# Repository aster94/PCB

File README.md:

# PCB

This is a repo to store some PCB I've made for various projects

In every folder there is a PCB with readme, images, the eagle/KiCad files and a zip archive with the gerber files. All licensed with CC-BY-SA

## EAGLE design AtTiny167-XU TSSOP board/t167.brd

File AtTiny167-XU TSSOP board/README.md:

# AtTiny167-XU TSSOP board

### License

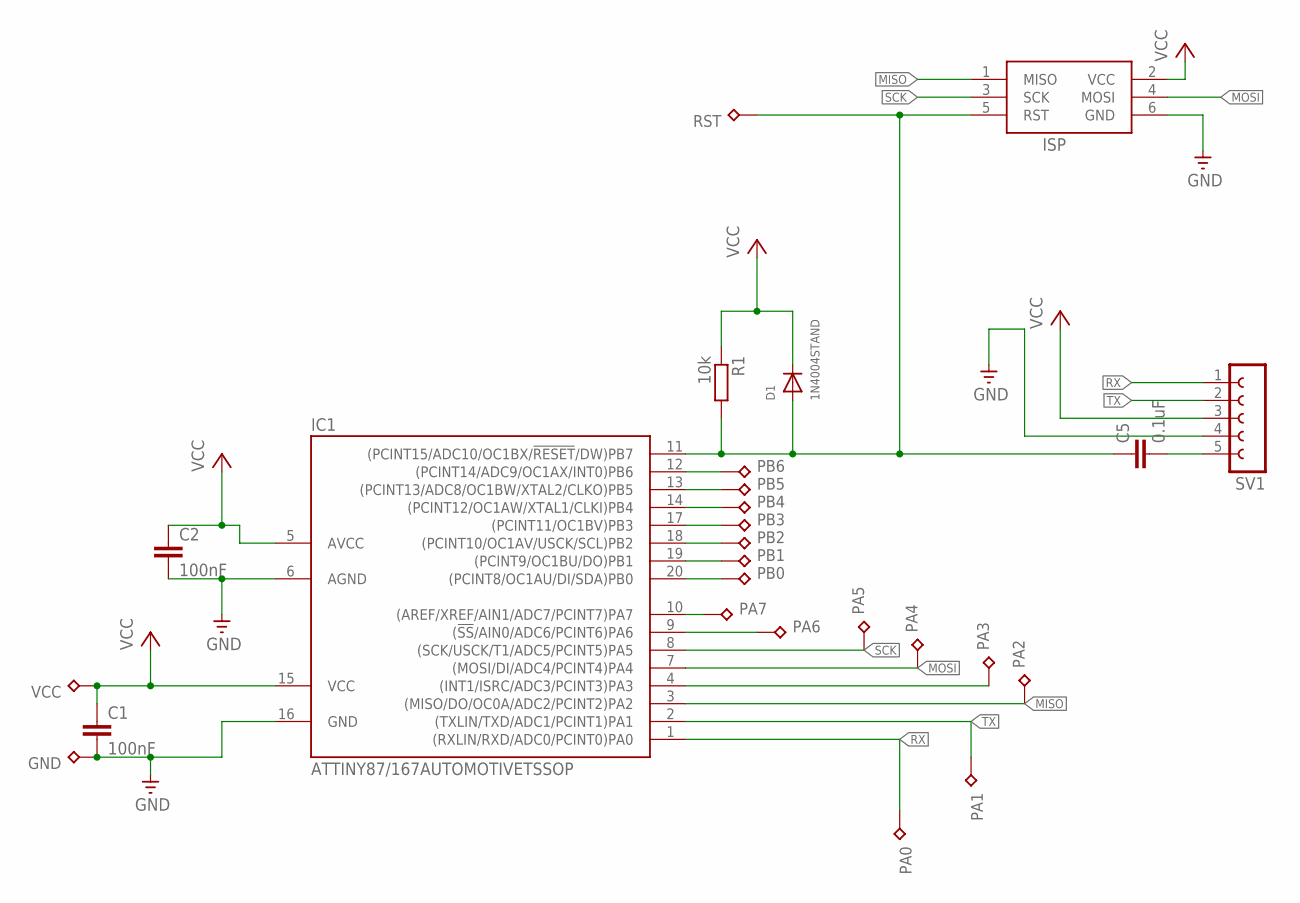
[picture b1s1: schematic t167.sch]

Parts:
C1, C2: 100nF; C0805
C5: 0.1uF; C0805K
D1: 1N4004STAND; SOD-323F
GND: 1XPIN-HEADER
IC1: ATTINY87/167AUTOMOTIVETSSOP; TSSOP20
ISP: AVRISP-6; AVRISP
PA0, PA1, PA2, PA3, PA4, PA5, PA6, PA7: 1XPIN-HEADER
PB0, PB1, PB2, PB3, PB4, PB5, PB6: 1XPIN-HEADER
R1: 10k; M0805
RST: 1XPIN-HEADER
SV1: FE05-1
VCC: 1XPIN-HEADER

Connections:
GND: C1.2, C2.2, GND.P$1, IC1.6 (AGND), IC1.16 (GND), ISP.6 (GND), SV1.4
MISO: IC1.3 ((MISO/DO/OC0A/ADC2/PCINT2)PA2), ISP.1 (MISO), PA2.P$1
MOSI: IC1.7 ((MOSI/DI/ADC4/PCINT4)PA4), ISP.4 (MOSI), PA4.P$1
unnamed: IC1.4 ((INT1/ISRC/ADC3/PCINT3)PA3), PA3.P$1
unnamed: C5.2, SV1.5
unnamed: IC1.9 ((!SS!/AIN0/ADC6/PCINT6)PA6), PA6.P$1
unnamed: IC1.10 ((AREF/XREF/AIN1/ADC7/PCINT7)PA7), PA7.P$1
unnamed: IC1.18 ((PCINT10/OC1AV/USCK/SCL)PB2), PB2.P$1
unnamed: IC1.20 ((PCINT8/OC1AU/DI/SDA)PB0), PB0.P$1
unnamed: IC1.19 ((PCINT9/OC1BU/DO)PB1), PB1.P$1
unnamed: IC1.17 ((PCINT11/OC1BV)PB3), PB3.P$1
unnamed: IC1.14 ((PCINT12/OC1AW/XTAL1/CLKI)PB4), PB4.P$1
unnamed: IC1.13 ((PCINT13/ADC8/OC1BW/XTAL2/CLKO)PB5), PB5.P$1
unnamed: IC1.12 ((PCINT14/ADC9/OC1AX/INT0)PB6), PB6.P$1
RST: C5.1, D1.A, IC1.11 ((PCINT15/ADC10/OC1BX/!RESET!/DW)PB7), ISP.5 (RST), R1.2, RST.P$1
RX: IC1.1 ((RXLIN/RXD/ADC0/PCINT0)PA0), PA0.P$1, SV1.1
SCK: IC1.8 ((SCK/USCK/T1/ADC5/PCINT5)PA5), ISP.3 (SCK), PA5.P$1
TX: IC1.2 ((TXLIN/TXD/ADC1/PCINT1)PA1), PA1.P$1, SV1.2
VCC: C1.1, C2.1, D1.C, IC1.5 (AVCC), IC1.15 (VCC), ISP.2 (VCC), R1.1, SV1.3, VCC.P$1

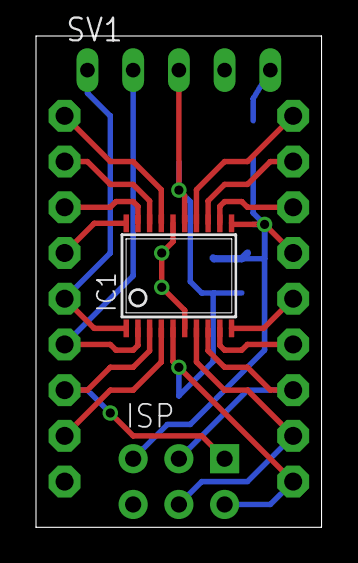
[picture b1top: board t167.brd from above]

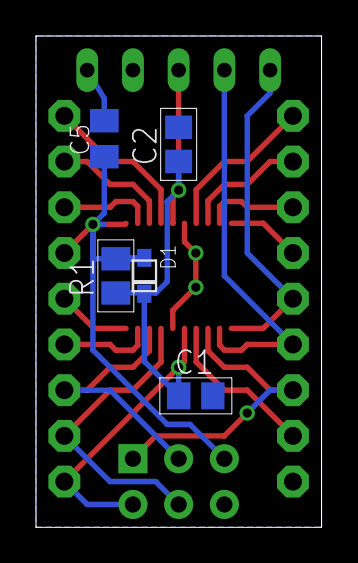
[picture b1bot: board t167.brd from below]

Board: 2 copper layers, 15.9 x 27.3 mm, 26 parts (5 on the bottom side), 19 nets.

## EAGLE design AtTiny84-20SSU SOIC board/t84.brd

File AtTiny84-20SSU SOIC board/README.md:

# AtTiny84-20SSU SOIC board

### License

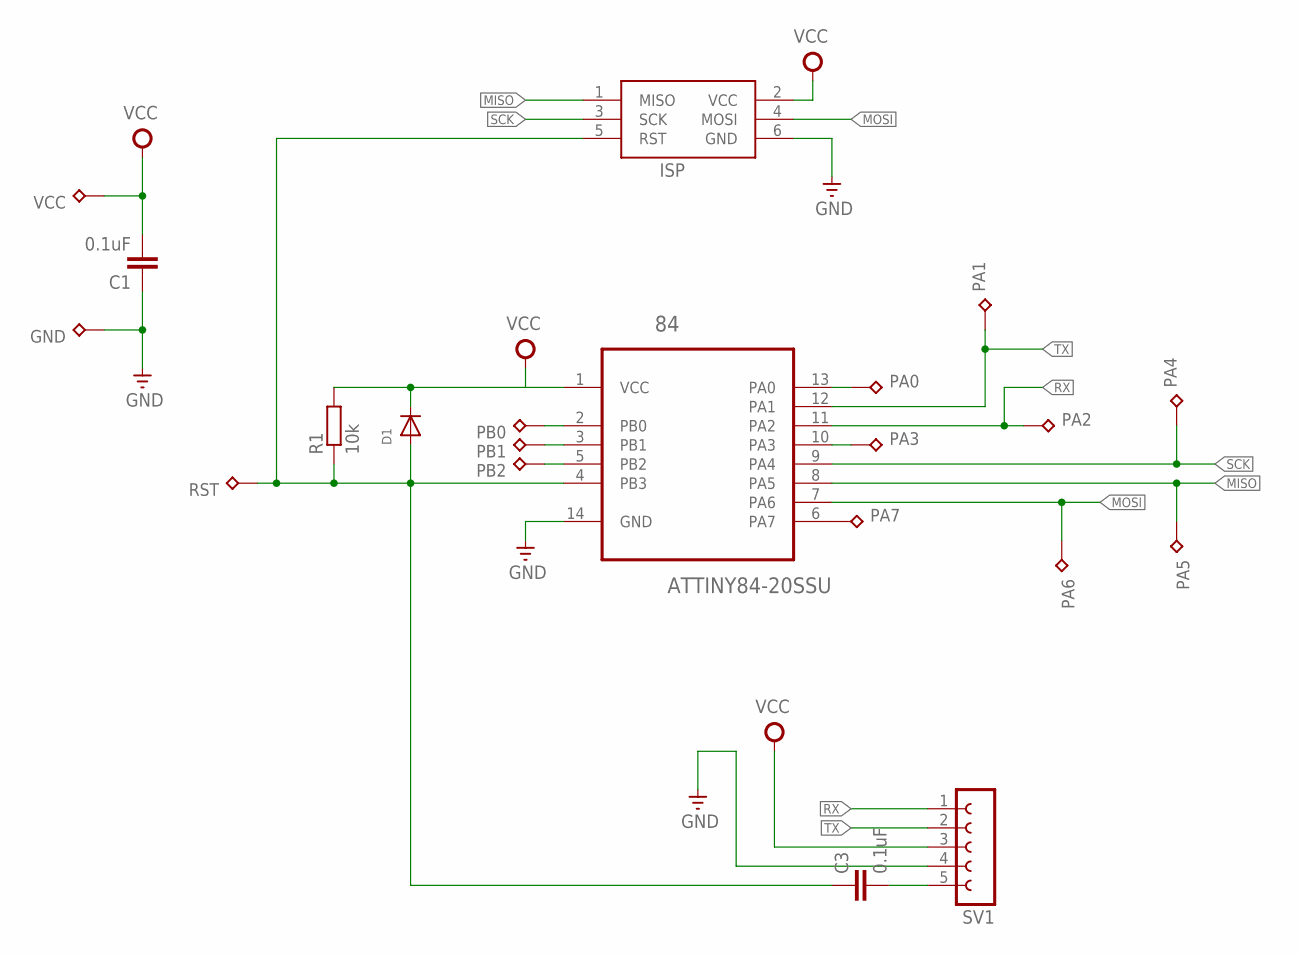
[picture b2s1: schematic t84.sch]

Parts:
84: ATTINY84-20SSU; SOIC127P600X175-14N
C1, C3: 0.1uF; C0805K
D1: DIODESOD-123; SOD-123
GND: 1XPIN-HEADER
ISP: AVRISP-6; AVRISP
PA0, PA1, PA2, PA3, PA4, PA5, PA6, PA7: 1XPIN-HEADER
PB0, PB1, PB2: 1XPIN-HEADER
R1: 10k; M0805
RST: 1XPIN-HEADER
SV1: FE05-1
VCC: 1XPIN-HEADER

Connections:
GND: 84.14 (GND), C1.1, GND.P$1, ISP.6 (GND), SV1.4
MISO: 84.8 (PA5), ISP.1 (MISO), PA5.P$1
MOSI: 84.7 (PA6), ISP.4 (MOSI), PA6.P$1
unnamed: C3.2, SV1.5
unnamed: 84.2 (PB0), PB0.P$1
unnamed: 84.3 (PB1), PB1.P$1
unnamed: 84.5 (PB2), PB2.P$1
unnamed: 84.6 (PA7), PA7.P$1
unnamed: 84.13 (PA0), PA0.P$1
unnamed: 84.10 (PA3), PA3.P$1
RST: 84.4 (PB3), C3.1, D1.A, ISP.5 (RST), R1.1, RST.P$1
RX: 84.11 (PA2), PA2.P$1, SV1.1
SCK: 84.9 (PA4), ISP.3 (SCK), PA4.P$1
TX: 84.12 (PA1), PA1.P$1, SV1.2
VCC: 84.1 (VCC), C1.2, D1.C, ISP.2 (VCC), R1.2, SV1.3, VCC.P$1

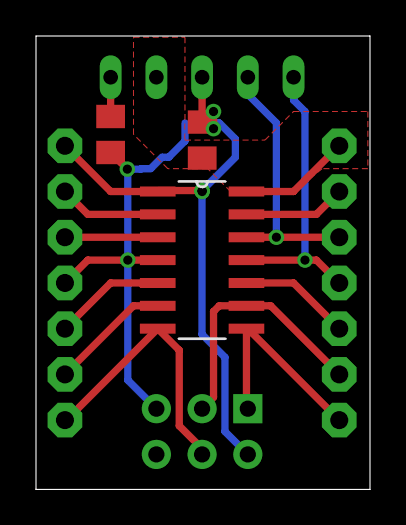
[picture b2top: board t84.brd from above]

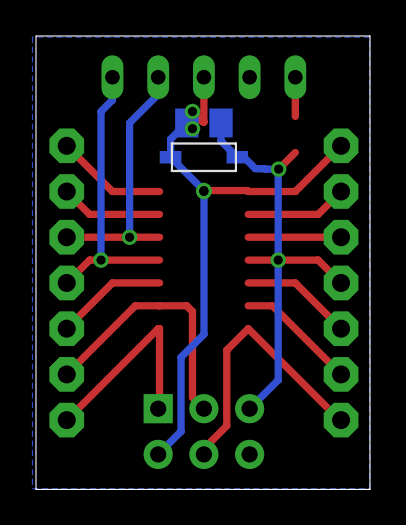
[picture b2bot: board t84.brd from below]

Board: 2 copper layers, 18.6 x 25.2 mm, 21 parts (2 on the bottom side), 15 nets.

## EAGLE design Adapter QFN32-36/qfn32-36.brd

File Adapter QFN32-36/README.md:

# Adapter QFN32-36

### License

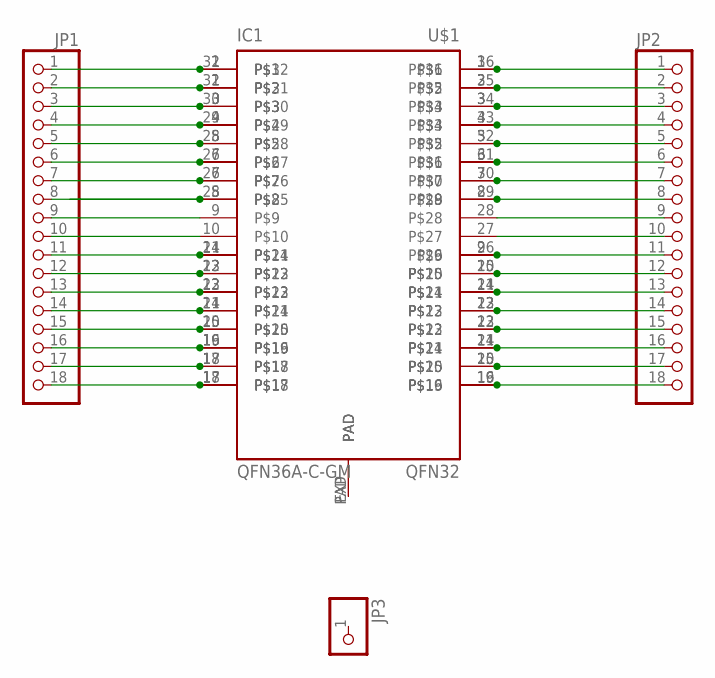
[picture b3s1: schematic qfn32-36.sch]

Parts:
IC1: QFN36A-C-GM; QFN36-6X6
JP1, JP2: PINHD-1X18-BIG; 1X18-BIG
JP3: PINHD-1X1; 1X01
U$1: QFN32; QFN32-5X5

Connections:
unnamed: IC1.1, JP1.1, U$1.32
unnamed: IC1.2, JP1.2, U$1.31
unnamed: IC1.3, JP1.3, U$1.30
unnamed: IC1.4, JP1.4, U$1.29
unnamed: IC1.5, JP1.5, U$1.28
unnamed: IC1.6, JP1.6, U$1.27
unnamed: IC1.7, JP1.7, U$1.26
unnamed: IC1.8, JP1.8, U$1.25
unnamed: IC1.10, JP1.10
unnamed: IC1.9, JP1.9
unnamed: IC1.11, JP1.11, U$1.24
unnamed: IC1.12, JP1.12, U$1.23
unnamed: IC1.13, JP1.13, U$1.22
unnamed: IC1.14, JP1.14, U$1.21
unnamed: IC1.15, JP1.15, U$1.20
unnamed: IC1.16, JP1.16, U$1.19
unnamed: IC1.17, JP1.17, U$1.18
unnamed: IC1.18, JP1.18, U$1.17
unnamed: IC1.36, JP2.1, U$1.1
unnamed: IC1.35, JP2.2, U$1.2
unnamed: IC1.34, JP2.3, U$1.3
unnamed: IC1.33, JP2.4, U$1.4
unnamed: IC1.32, JP2.5, U$1.5
unnamed: IC1.31, JP2.6, U$1.6
unnamed: IC1.30, JP2.7, U$1.7
unnamed: IC1.29, JP2.8, U$1.8
unnamed: IC1.28, JP2.9
unnamed: IC1.27, JP2.10
unnamed: IC1.26, JP2.11, U$1.9
unnamed: IC1.25, JP2.12, U$1.10
unnamed: IC1.24, JP2.13, U$1.11
unnamed: IC1.23, JP2.14, U$1.12
unnamed: IC1.22, JP2.15, U$1.13
unnamed: IC1.21, JP2.16, U$1.14
unnamed: IC1.19, JP2.18, U$1.16
unnamed: IC1.20, JP2.17, U$1.15
unnamed: JP3.1, U$1.PAD

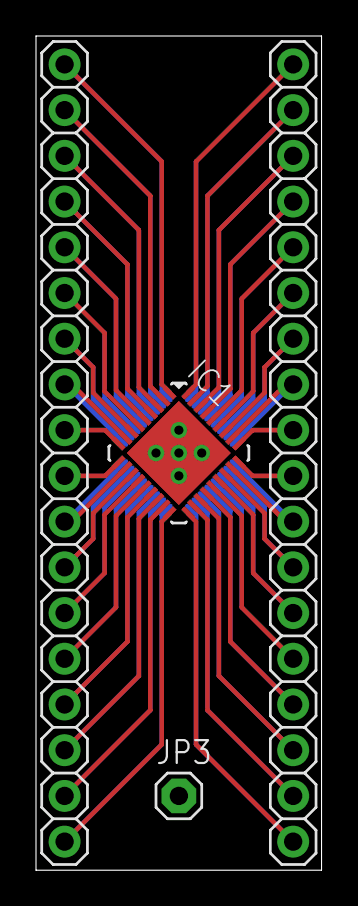
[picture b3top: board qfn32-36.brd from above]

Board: 2 copper layers, 15.9 x 46.3 mm, 5 parts (1 on the bottom side), 37 nets.

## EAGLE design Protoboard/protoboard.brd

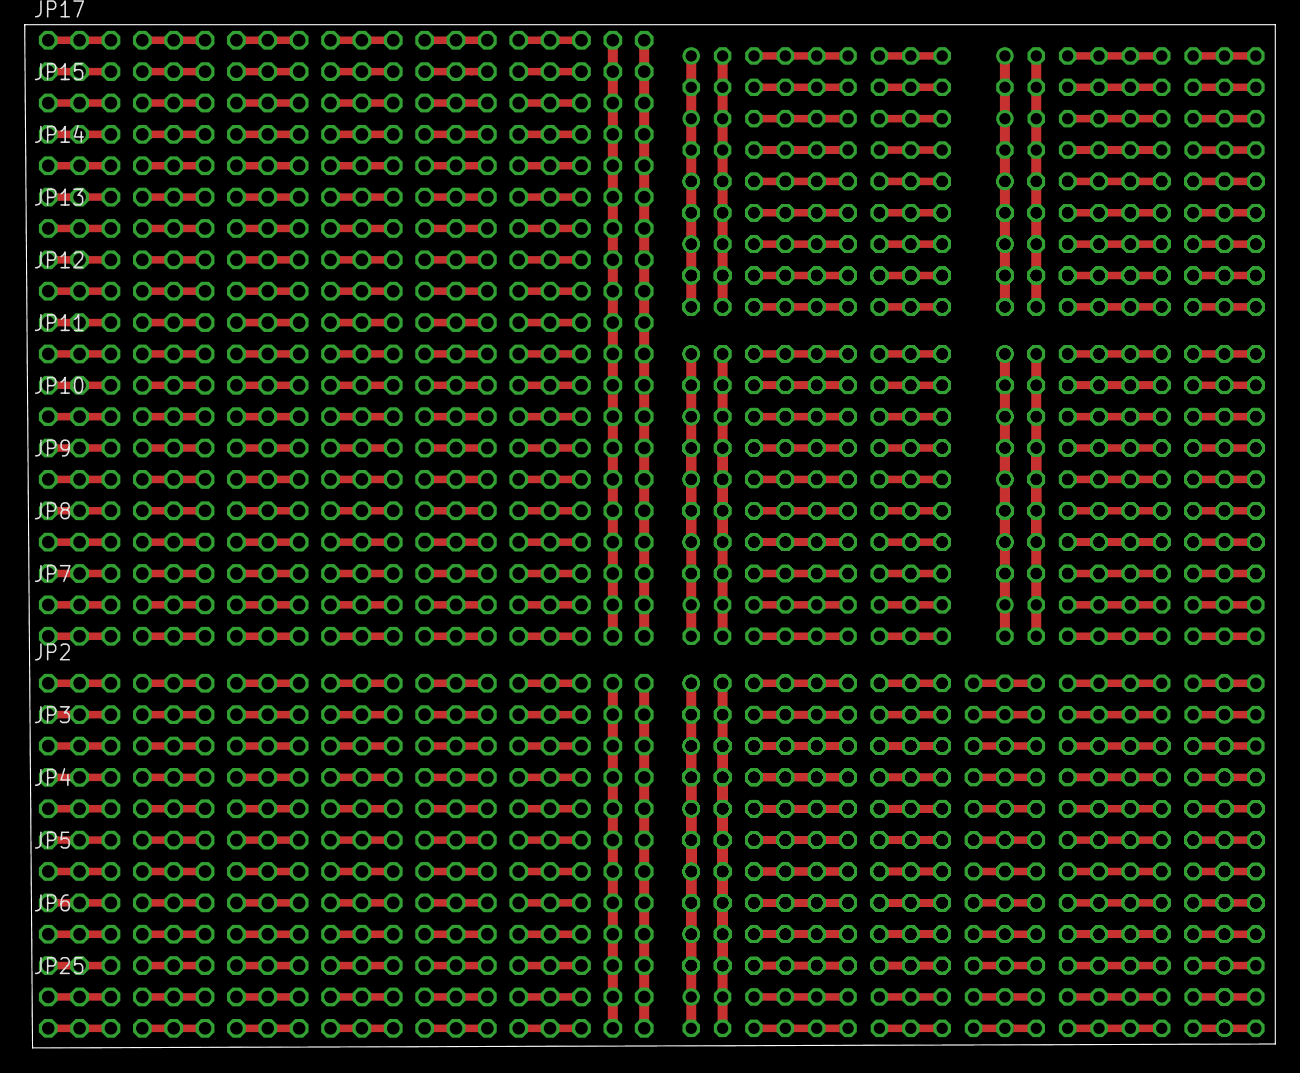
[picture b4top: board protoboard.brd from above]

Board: 2 copper layers, 101.3 x 82.9 mm, 80 parts (0 on the bottom side), 208 nets.

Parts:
E$1, E$2, E$3, E$4, E$5, E$6, E$7, E$8, E$9, E$10, E$11, E$12, E$13, E$14, E$15, E$16, E$17, E$18, E$19, E$20, E$21, E$22, E$23, E$24, E$25, E$26, E$27, E$28, E$29, E$30, E$31, E$32, E$33, E$34, E$35, E$36, E$37, E$38, E$39, E$40, E$41, E$42, E$43, E$44, E$45, E$46, E$47, E$48, E$49, E$50, E$51, E$52, E$53, E$54, E$55, E$56, E$57, E$58, E$59, E$60, E$61, E$62, E$63, E$64: FE09-2
JP2, JP3, JP4, JP5, JP6, JP7, JP8, JP9, JP10, JP11, JP12, JP13, JP14, JP15, JP17, JP25: 2X20

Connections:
unnamed: JP25.2, JP25.6
unnamed: JP25.8, JP25.12
unnamed: JP25.14, JP25.18
unnamed: JP25.20, JP25.24
unnamed: JP25.26, JP25.30
unnamed: JP25.32, JP25.36
unnamed: JP25.37, JP25.38
unnamed: JP25.1, JP25.5
unnamed: JP25.7, JP25.11
unnamed: JP25.13, JP25.17
unnamed: JP25.19, JP25.23
unnamed: JP25.25, JP25.29
unnamed: JP25.31, JP25.35
unnamed: JP2.2, JP2.6
unnamed: JP2.8, JP2.12
unnamed: JP2.14, JP2.18
unnamed: JP2.20, JP2.24
unnamed: JP2.26, JP2.30
unnamed: JP2.32, JP2.36
unnamed: JP2.37, JP2.38
unnamed: JP2.39, JP2.40
unnamed: JP2.1, JP2.5
unnamed: JP2.7, JP2.11
unnamed: JP2.13, JP2.17
unnamed: JP2.19, JP2.23
unnamed: JP2.25, JP2.29
unnamed: JP2.31, JP2.35
unnamed: JP3.2, JP3.6
unnamed: JP3.8, JP3.12
unnamed: JP3.14, JP3.18
unnamed: JP3.20, JP3.24
unnamed: JP3.26, JP3.30
unnamed: JP3.32, JP3.36
unnamed: JP3.37, JP3.38
unnamed: JP3.39, JP3.40
unnamed: JP3.1, JP3.5
unnamed: JP3.7, JP3.11
unnamed: JP3.13, JP3.17
unnamed: JP3.19, JP3.23
unnamed: JP3.25, JP3.29
unnamed: JP3.31, JP3.35
unnamed: JP4.2, JP4.6
unnamed: JP4.8, JP4.12
unnamed: JP4.14, JP4.18
unnamed: JP4.20, JP4.24
unnamed: JP4.26, JP4.30
unnamed: JP4.32, JP4.36
unnamed: JP4.37, JP4.38
unnamed: JP4.39, JP4.40
unnamed: JP4.1, JP4.5
unnamed: JP4.7, JP4.11
unnamed: JP4.13, JP4.17
unnamed: JP4.19, JP4.23
unnamed: JP4.25, JP4.29
unnamed: JP4.31, JP4.35
unnamed: JP5.2, JP5.6
unnamed: JP5.8, JP5.12
unnamed: JP5.14, JP5.18
unnamed: JP5.20, JP5.24
unnamed: JP5.26, JP5.30
unnamed: JP5.32, JP5.36
unnamed: JP5.37, JP5.38
unnamed: JP5.39, JP5.40
unnamed: JP5.1, JP5.5
unnamed: JP5.7, JP5.11
unnamed: JP5.13, JP5.17
unnamed: JP5.19, JP5.23
unnamed: JP5.25, JP5.29
unnamed: JP5.31, JP5.35
unnamed: JP6.2, JP6.6
unnamed: JP6.8, JP6.12
unnamed: JP6.14, JP6.18
unnamed: JP6.20, JP6.24
unnamed: JP6.26, JP6.30
unnamed: JP6.32, JP6.36
unnamed: JP6.37, JP6.38
unnamed: JP6.39, JP6.40
unnamed: JP6.1, JP6.5
unnamed: JP6.7, JP6.11
unnamed: JP6.13, JP6.17
unnamed: JP6.19, JP6.23
unnamed: JP6.25, JP6.29
unnamed: JP6.31, JP6.35
unnamed: JP7.2, JP7.6
unnamed: JP7.8, JP7.12
unnamed: JP7.14, JP7.18
unnamed: JP7.20, JP7.24
unnamed: JP7.26, JP7.30
unnamed: JP7.32, JP7.36
unnamed: JP7.37, JP7.38
unnamed: JP7.39, JP7.40
unnamed: JP7.1, JP7.5
unnamed: JP7.7, JP7.11
unnamed: JP7.13, JP7.17
unnamed: JP7.19, JP7.23
unnamed: JP7.25, JP7.29
unnamed: JP7.31, JP7.35
unnamed: JP8.2, JP8.6
unnamed: JP8.8, JP8.12
unnamed: JP8.14, JP8.18
unnamed: JP8.20, JP8.24
unnamed: JP8.26, JP8.30
unnamed: JP8.32, JP8.36
unnamed: JP8.37, JP8.38
unnamed: JP8.39, JP8.40
unnamed: JP8.1, JP8.5
unnamed: JP8.7, JP8.11
unnamed: JP8.13, JP8.17
unnamed: JP8.19, JP8.23
unnamed: JP8.25, JP8.29
unnamed: JP8.31, JP8.35
unnamed: JP9.2, JP9.6
unnamed: JP9.8, JP9.12
unnamed: JP9.14, JP9.18
unnamed: JP9.20, JP9.24
unnamed: JP9.26, JP9.30
unnamed: JP9.32, JP9.36
unnamed: JP9.37, JP9.38
unnamed: JP9.39, JP9.40
unnamed: JP9.1, JP9.5
unnamed: JP9.7, JP9.11
unnamed: JP9.13, JP9.17
unnamed: JP9.19, JP9.23
unnamed: JP9.25, JP9.29
unnamed: JP9.31, JP9.35
unnamed: JP10.2, JP10.6
unnamed: JP10.8, JP10.12
unnamed: JP10.14, JP10.18
unnamed: JP10.20, JP10.24
unnamed: JP10.26, JP10.30
unnamed: JP10.32, JP10.36
unnamed: JP10.37, JP10.38
unnamed: JP10.39, JP10.40
unnamed: JP10.1, JP10.5
unnamed: JP10.7, JP10.11
unnamed: JP10.13, JP10.17
unnamed: JP10.19, JP10.23
unnamed: JP10.25, JP10.29
unnamed: JP10.31, JP10.35
unnamed: JP11.2, JP11.6
unnamed: JP11.8, JP11.12
unnamed: JP11.14, JP11.18
unnamed: JP11.20, JP11.24
unnamed: JP11.26, JP11.30
unnamed: JP11.32, JP11.36
unnamed: JP11.37, JP11.38
unnamed: JP11.39, JP11.40
unnamed: JP11.1, JP11.5
unnamed: JP11.7, JP11.11
unnamed: JP11.13, JP11.17
unnamed: JP11.19, JP11.23
unnamed: JP11.25, JP11.29
unnamed: JP11.31, JP11.35
unnamed: JP12.2, JP12.6
unnamed: JP12.8, JP12.12
unnamed: JP12.14, JP12.18
unnamed: JP12.20, JP12.24
unnamed: JP12.26, JP12.30
unnamed: JP12.32, JP12.36
unnamed: JP12.37, JP12.38
unnamed: JP12.39, JP12.40
unnamed: JP12.1, JP12.5
unnamed: JP12.7, JP12.11
unnamed: JP12.13, JP12.17
unnamed: JP12.19, JP12.23
unnamed: JP12.25, JP12.29
unnamed: JP12.31, JP12.35
unnamed: JP13.2, JP13.6
unnamed: JP13.8, JP13.12
unnamed: JP13.14, JP13.18
unnamed: JP13.20, JP13.24
unnamed: JP13.26, JP13.30
unnamed: JP13.32, JP13.36
unnamed: JP13.37, JP13.38
unnamed: JP13.39, JP13.40
unnamed: JP13.1, JP13.5
unnamed: JP13.7, JP13.11
unnamed: JP13.13, JP13.17
unnamed: JP13.19, JP13.23
unnamed: JP13.25, JP13.29
unnamed: JP13.31, JP13.35
unnamed: JP14.2, JP14.6
unnamed: JP14.8, JP14.12
unnamed: JP14.14, JP14.18
unnamed: JP14.20, JP14.24
unnamed: JP14.26, JP14.30
unnamed: JP14.32, JP14.36
unnamed: JP14.37, JP14.38
unnamed: JP14.39, JP14.40
unnamed: JP14.1, JP14.5
unnamed: JP14.7, JP14.11
unnamed: JP14.13, JP14.17
unnamed: JP14.19, JP14.23
unnamed: JP14.25, JP14.29
unnamed: JP14.31, JP14.35
unnamed: JP15.2, JP15.6
unnamed: JP15.8, JP15.12
unnamed: JP15.14, JP15.18
unnamed: JP15.20, JP15.24
unnamed: JP15.26, JP15.30
unnamed: JP15.32, JP15.36
unnamed: JP15.39, JP15.40
unnamed: JP15.1, JP15.5
unnamed: JP15.7, JP15.11
unnamed: JP15.13, JP15.17
unnamed: JP15.19, JP15.23
unnamed: JP15.25, JP15.29
unnamed: JP15.31, JP15.35

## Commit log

2018-04-11 Rename Protoboard/protoboard.brd to Stripboard/stripboard.brd
2019-03-01 added images and readme
2019-03-01 Create LICENSE
